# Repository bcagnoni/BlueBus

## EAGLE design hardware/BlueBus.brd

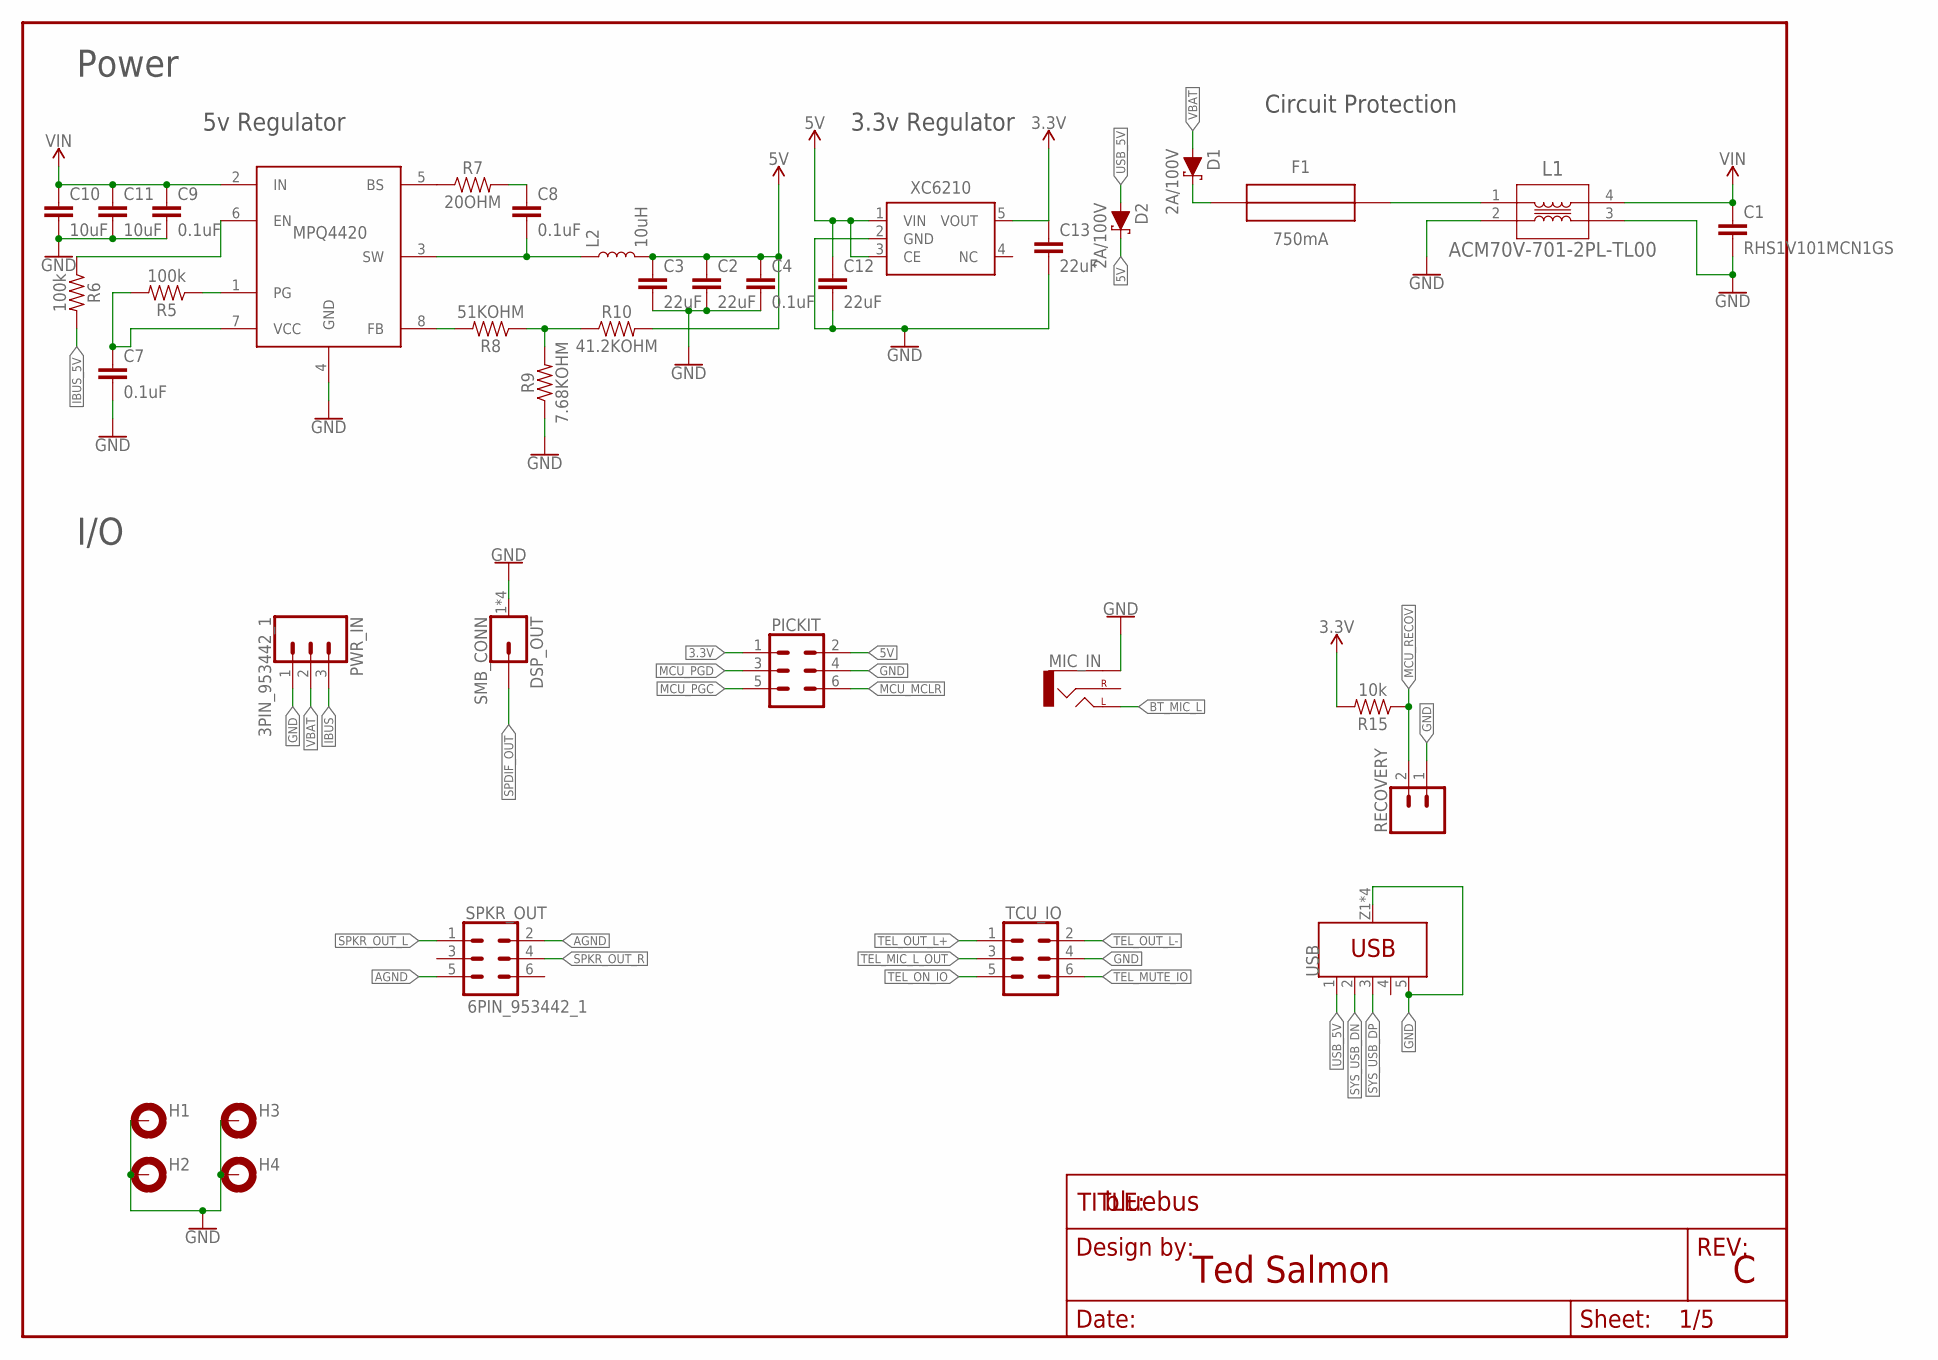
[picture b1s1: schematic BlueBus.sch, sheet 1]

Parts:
C1: RHS1V101MCN1GS
C2, C3, C12, C13: 22uF; 0805
C4, C7, C8, C9: 0.1uF; 0805
C10, C11: 10uF; 1206
D1, D2: 2A/100V; SOD123
DSP_OUT: SMB_CONN; MOLEX_SMB
F1: 750mA; LITTLEFUSE
FRAME1: FRAME-LETTER; DUMMY
H1, H2, H3, H4: 2,0-PAD; 2.0-PAD
L1: ACM70V-701-2PL-TL00
L2: 10uH; MPL-SE5040
MIC_IN: AUDIO-CUI-SJ-3523-SMT; AUDIO-CUI-SJ-352X-SMT
MPQ4420: MPQ4420; TSOT23-8
PICKIT: 6PIN_JUMPER; 2X3
PWR_IN: 3PIN_953442_1; TE_MQS_3PIN
R5, R6: 100k; 0805
R7: 20OHM; 0805
R8: 51KOHM; 0805
R9: 7.68KOHM; 0805
R10: 41.2KOHM; 0805
R15: 10k; 0805
RECOVERY: 2PIN_JUMPER; 1X02
SPKR_OUT: 6PIN_953442_1; TE_MQS_6PIN
TCU_IO: 6PIN_5_103166_1; TE_AMPMODU_6_PIN
USB: USB_WURTH_629105150521; 629105150521
XC6210: XC6210SOT25; SOT23-5

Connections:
3.3V: C13.1, PICKIT.1, R15.2, XC6210.5 (VOUT); also elsewhere on the board
5V: C2.1, C3.1, C4.1, C12.1, D2.C, L2.2, PICKIT.2, R10.2, XC6210.1 (VIN), XC6210.3 (CE); also elsewhere on the board
5VREG_BS: MPQ4420.5 (BS), R7.1
5VREG_BS_CAP: C8.1, R7.2
5VREG_EN: MPQ4420.6 (EN), R6.1
5VREG_FB: MPQ4420.8 (FB), R8.2
5VREG_FB_T: R8.1, R9.2, R10.1
5VREG_PG: MPQ4420.1 (PG), R5.1
5VREG_SW: C8.2, L2.1, MPQ4420.3 (SW)
5VREG_VCC: C7.1, MPQ4420.7 (VCC), R5.2
AGND: SPKR_OUT.2, SPKR_OUT.5; also elsewhere on the board
BT_MIC_L: MIC_IN.TIP (LEFT); also elsewhere on the board
GND: C1.2, C2.2, C3.2, C4.2, C7.2, C9.2, C10.2, C11.2, C12.2, C13.2, DSP_OUT.1 (GND), DSP_OUT.2 (GND), DSP_OUT.3 (GND), DSP_OUT.4 (GND), H1.B2,0, H2.B2,0, H3.B2,0, H4.B2,0, L1.2, L1.3, MIC_IN.SLEEVE, MPQ4420.4 (GND), PICKIT.4, PWR_IN.1, R9.1, RECOVERY.1, TCU_IO.4, USB.5 (GND), USB.Z1 (SHIELD), USB.Z2 (SHIELD), USB.Z3 (SHIELD), USB.Z4 (SHIELD), XC6210.2 (GND); also elsewhere on the board
IBUS: PWR_IN.3; also elsewhere on the board
IBUS_5V: R6.2; also elsewhere on the board
MCU_MCLR: PICKIT.6; also elsewhere on the board
MCU_PGC: PICKIT.5; also elsewhere on the board
MCU_PGD: PICKIT.3; also elsewhere on the board
MCU_RECOV: R15.1, RECOVERY.2; also elsewhere on the board
SPDIF_OUT: DSP_OUT.P$1 (1); also elsewhere on the board
SPKR_OUT_L: SPKR_OUT.1; also elsewhere on the board
SPKR_OUT_R: SPKR_OUT.4; also elsewhere on the board
SYS_USB_DN: USB.2 (D-); also elsewhere on the board
SYS_USB_DP: USB.3 (D+); also elsewhere on the board
TEL_MIC_L_OUT: TCU_IO.3; also elsewhere on the board
TEL_MUTE_IO: TCU_IO.6; also elsewhere on the board
TEL_ON_IO: TCU_IO.5; also elsewhere on the board
TEL_OUT_L+: TCU_IO.1; also elsewhere on the board
TEL_OUT_L-: TCU_IO.2; also elsewhere on the board
USB_5V: D2.A, USB.1 (VBUS)
VBAT: D1.A, PWR_IN.2
VBAT_DIODE: D1.C, F1.IN (OUT)
VBAT_FUSE: F1.OUT (IN), L1.1
VIN: C1.1, C9.1, C10.1, C11.1, L1.4, MPQ4420.2 (IN); also elsewhere on the board

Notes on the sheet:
Ted Salmon
Power
I/O
3.3v Regulator
5v Regulator
Circuit Protection

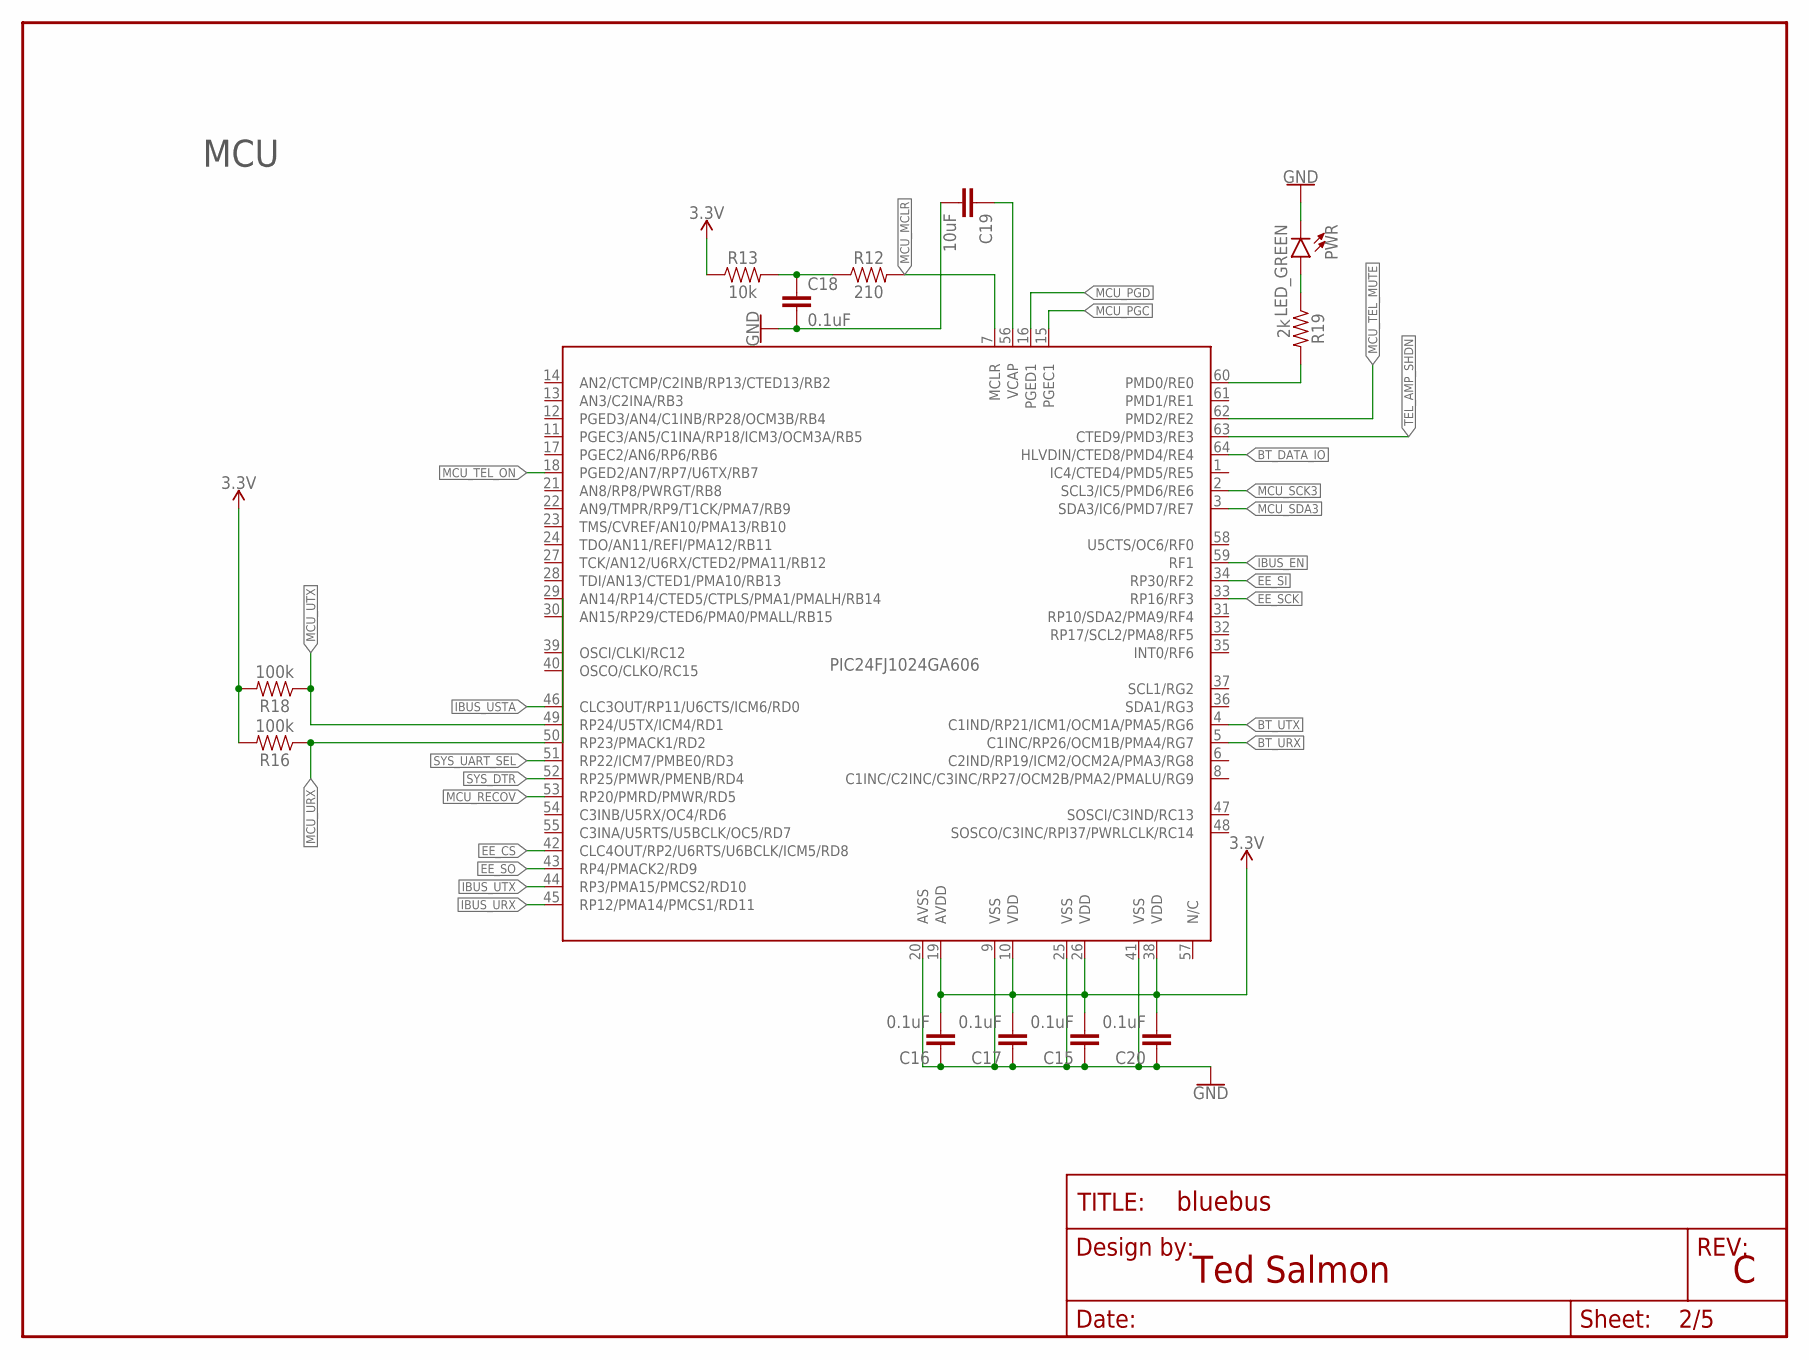
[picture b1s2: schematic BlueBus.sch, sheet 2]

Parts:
C15, C16, C17, C18, C20: 0.1uF; 0805
C19: 10uF; 0805
FRAME2: FRAME-LETTER; DUMMY
PIC24FJ1024GA606: PIC24FJ1024GA606; TQFP64
PWR: LED_GREEN; LED-0805
R12: 210; 0805
R13: 10k; 0805
R16, R18: 100k; 0805
R19: 2k; 0805

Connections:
3.3V: C15.2, C16.2, C17.2, C20.2, PIC24FJ1024GA606.10 (VDD), PIC24FJ1024GA606.19 (AVDD), PIC24FJ1024GA606.26 (VDD), PIC24FJ1024GA606.38 (VDD), R13.1, R16.2, R18.2; also elsewhere on the board
BT_DATA_IO: PIC24FJ1024GA606.64 (HLVDIN/CTED8/PMD4/RE4); also elsewhere on the board
BT_URX: PIC24FJ1024GA606.5 (C1INC/RP26/OCM1B/PMA4/RG7); also elsewhere on the board
BT_UTX: PIC24FJ1024GA606.4 (C1IND/RP21/ICM1/OCM1A/PMA5/RG6); also elsewhere on the board
EE_CS: PIC24FJ1024GA606.42 (CLC4OUT/RP2/U6RTS/U6BCLK/ICM5/RD8); also elsewhere on the board
EE_SCK: PIC24FJ1024GA606.33 (RP16/RF3); also elsewhere on the board
EE_SI: PIC24FJ1024GA606.34 (RP30/RF2); also elsewhere on the board
EE_SO: PIC24FJ1024GA606.43 (RP4/PMACK2/RD9); also elsewhere on the board
GND: C15.1, C16.1, C17.1, C18.2, C19.2, C20.1, PIC24FJ1024GA606.9 (VSS), PIC24FJ1024GA606.20 (AVSS), PIC24FJ1024GA606.25 (VSS), PIC24FJ1024GA606.41 (VSS), PWR.- (C); also elsewhere on the board
IBUS_EN: PIC24FJ1024GA606.59 (RF1); also elsewhere on the board
IBUS_URX: PIC24FJ1024GA606.45 (RP12/PMA14/PMCS1/RD11); also elsewhere on the board
IBUS_USTA: PIC24FJ1024GA606.46 (CLC3OUT/RP11/U6CTS/ICM6/RD0); also elsewhere on the board
IBUS_UTX: PIC24FJ1024GA606.44 (RP3/PMA15/PMCS2/RD10); also elsewhere on the board
MCU_MCLR: PIC24FJ1024GA606.7 (MCLR), R12.2; also elsewhere on the board
MCU_MCLR_RES: C18.1, R12.1, R13.2
MCU_ON_LED: PIC24FJ1024GA606.60 (PMD0/RE0), R19.2
MCU_ON_LED_RES: PWR.+ (A), R19.1
MCU_PGC: PIC24FJ1024GA606.15 (PGEC1); also elsewhere on the board
MCU_PGD: PIC24FJ1024GA606.16 (PGED1); also elsewhere on the board
MCU_RECOV: PIC24FJ1024GA606.53 (RP20/PMRD/PMWR/RD5); also elsewhere on the board
MCU_SCK3: PIC24FJ1024GA606.2 (SCL3/IC5/PMD6/RE6); also elsewhere on the board
MCU_SDA3: PIC24FJ1024GA606.3 (SDA3/IC6/PMD7/RE7); also elsewhere on the board
MCU_TEL_MUTE: PIC24FJ1024GA606.62 (PMD2/RE2); also elsewhere on the board
MCU_TEL_ON: PIC24FJ1024GA606.18 (PGED2/AN7/RP7/U6TX/RB7); also elsewhere on the board
MCU_URX: PIC24FJ1024GA606.50 (RP23/PMACK1/RD2), R16.1; also elsewhere on the board
MCU_UTX: PIC24FJ1024GA606.49 (RP24/U5TX/ICM4/RD1), R18.1; also elsewhere on the board
MCU_VCAP: C19.1, PIC24FJ1024GA606.56 (VCAP)
SYS_DTR: PIC24FJ1024GA606.52 (RP25/PMWR/PMENB/RD4); also elsewhere on the board
SYS_UART_SEL: PIC24FJ1024GA606.51 (RP22/ICM7/PMBE0/RD3); also elsewhere on the board
TEL_AMP_SHDN: PIC24FJ1024GA606.63 (CTED9/PMD3/RE3); also elsewhere on the board

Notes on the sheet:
Ted Salmon
MCU

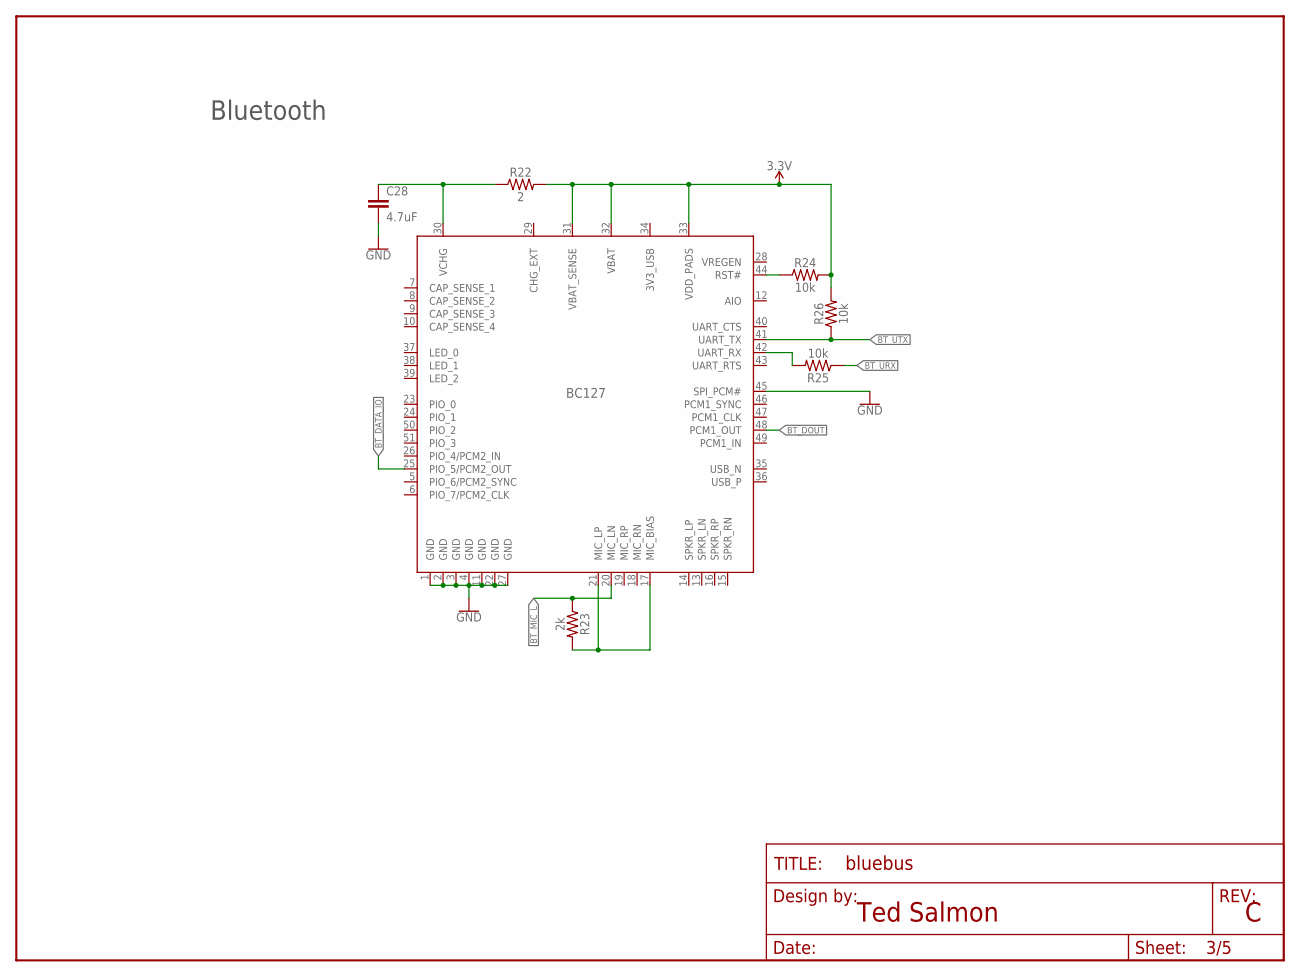
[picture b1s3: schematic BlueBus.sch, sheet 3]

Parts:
BC127: BC127
C28: 4.7uF; 0805
FRAME4: FRAME-LETTER; DUMMY
R22: 2; 0805
R23: 2k; 0805
R24, R25, R26: 10k; 0805

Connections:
3.3V: BC127.31 (VBAT_SENSE), BC127.32 (VBAT), BC127.33 (VDD_PADS), R22.2, R24.2, R26.2; also elsewhere on the board
3V3_USB: BC127.34 (3V3_USB)
BT_3V3_FILTER: BC127.30 (VCHG), C28.1, R22.1
BT_DATA_IO: BC127.25 (PIO_5/PCM2_OUT); also elsewhere on the board
BT_DOUT: BC127.48 (PCM1_OUT); also elsewhere on the board
BT_MIC_BIAS: BC127.17 (MIC_BIAS), BC127.21 (MIC_LP), R23.2
BT_MIC_L: BC127.20 (MIC_LN), R23.1; also elsewhere on the board
BT_RST: BC127.44 (RST#), R24.1
BT_URX: R25.1; also elsewhere on the board
BT_URX_RES: BC127.42 (UART_RX), R25.2
BT_UTX: BC127.41 (UART_TX), R26.1; also elsewhere on the board
CHG_EXT: BC127.29 (CHG_EXT)
GND: BC127.1 (GND), BC127.2 (GND), BC127.3 (GND), BC127.4 (GND), BC127.11 (GND), BC127.22 (GND), BC127.27 (GND), BC127.45 (SPI_PCM#), C28.2; also elsewhere on the board

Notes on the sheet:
Bluetooth
Ted Salmon

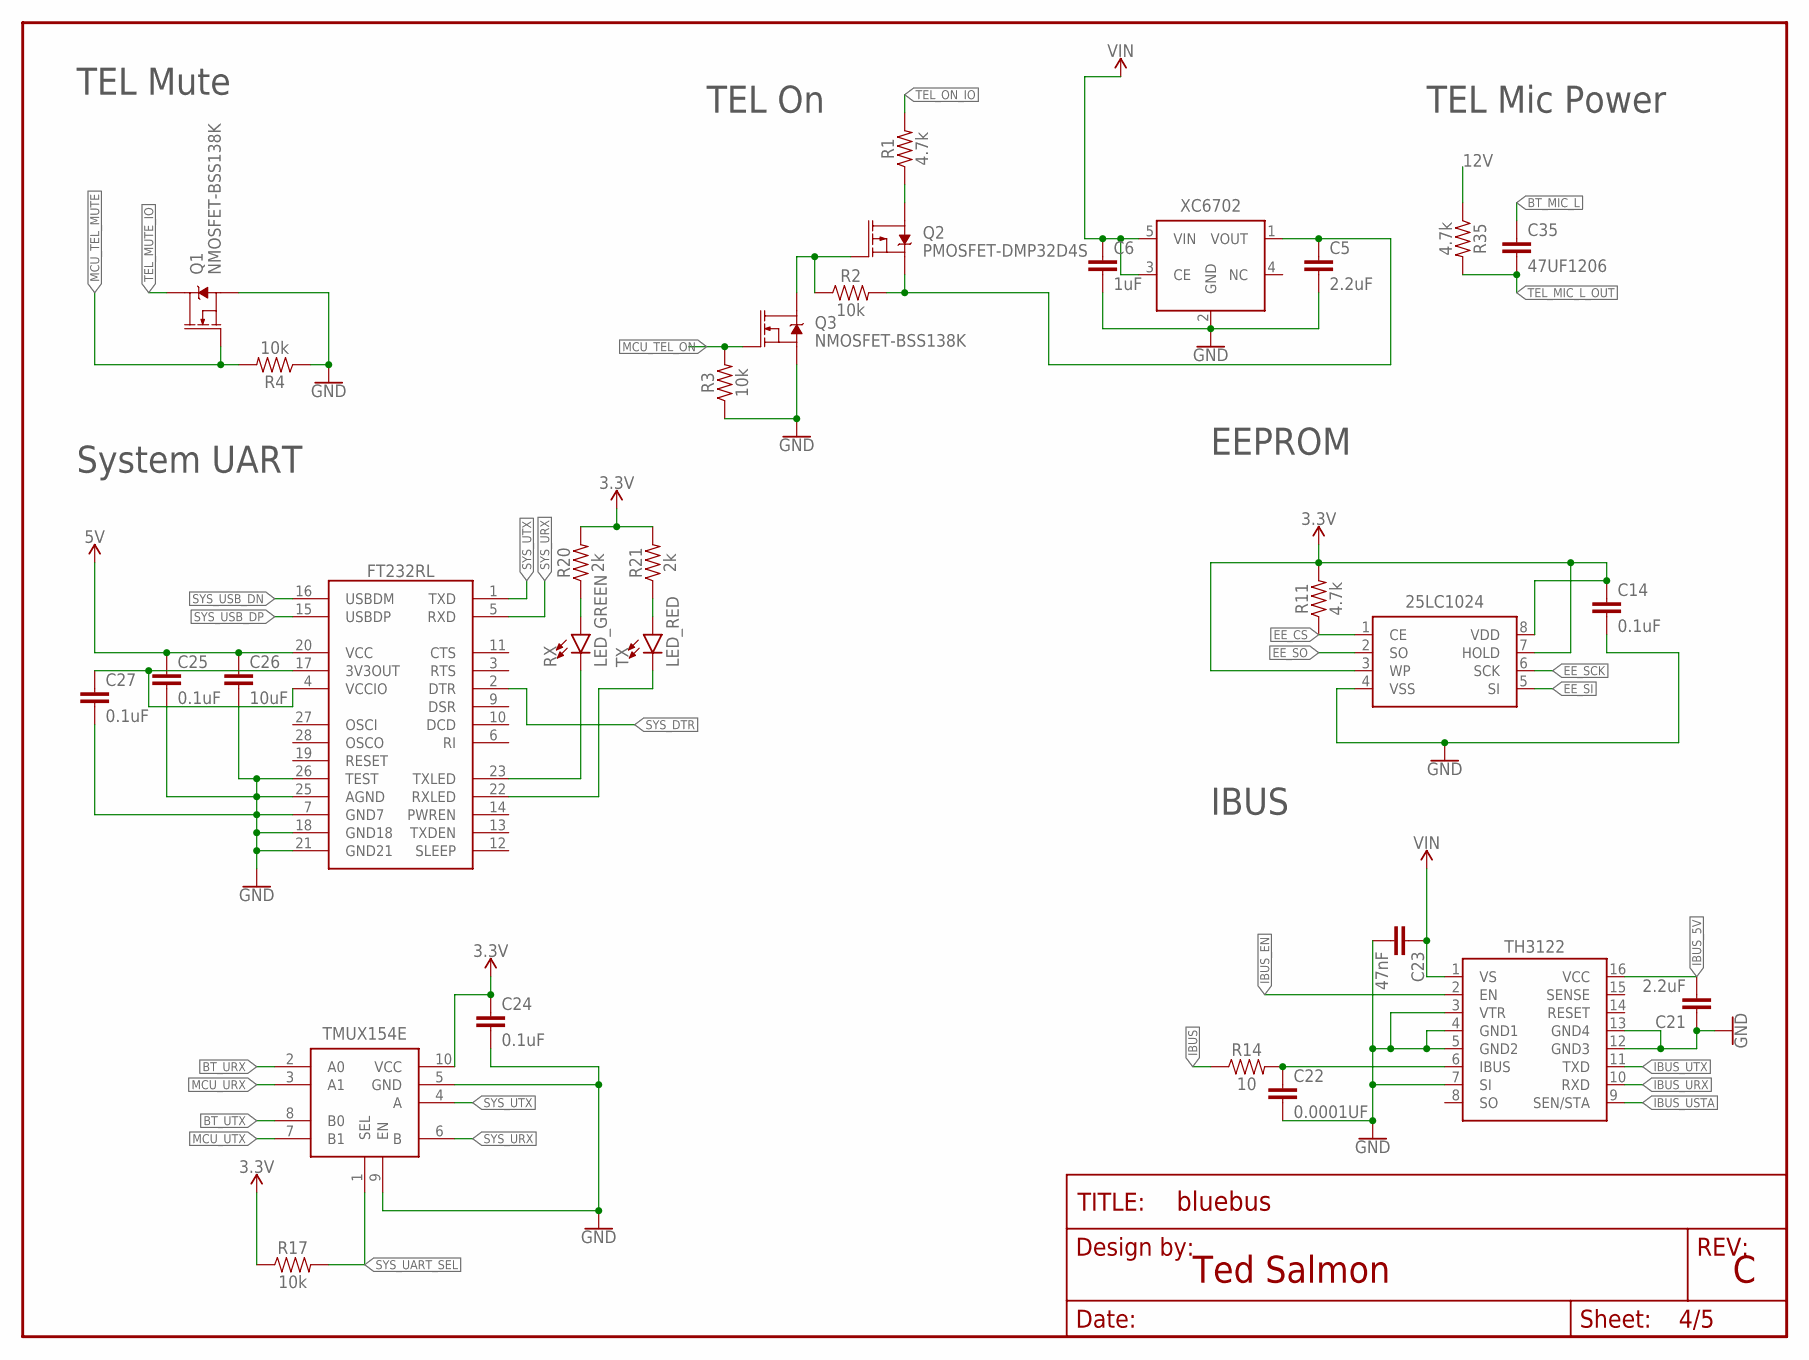
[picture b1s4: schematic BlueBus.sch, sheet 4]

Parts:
25LC1024: 25LC1024; SOIJ-8
C5, C21: 2.2uF; 0805
C6: 1uF; 0805
C14, C24, C25, C27: 0.1uF; 0805
C22: 0.0001UF; 0805
C23: 47nF; 0805
C26: 10uF; 0805
C35: 47UF1206; 1206
FRAME3: FRAME-LETTER; DUMMY
FT232RL: FT232RL; SSOP28
Q1, Q3: NMOSFET-BSS138K; SOT-23
Q2: PMOSFET-DMP32D4S; SOT-23
R1, R11, R35: 4.7k; 0805
R2, R3, R4, R17: 10k; 0805
R14: 10; 0805
R20, R21: 2k; 0805
RX: LED_GREEN; LED-0805
TH3122: TH3122.4; SOIC16DF
TMUX154E: TMUX154E; VSSOP10
TX: LED_RED; LED-0805
XC6702: XC6702DC018PR-G; SOT-89-5

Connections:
3.3V: 25LC1024.3 (WP), 25LC1024.7 (HOLD), 25LC1024.8 (VDD), C14.1, C24.1, R11.2, R17.1, R20.2, R21.2, TMUX154E.10 (VCC); also elsewhere on the board
5V: C25.1, C26.1, FT232RL.20 (VCC); also elsewhere on the board
12V: C5.1, Q2.2 (S), R2.2, R35.1, XC6702.1 (VOUT)
BT_MIC_L: C35.1; also elsewhere on the board
BT_URX: TMUX154E.2 (A0); also elsewhere on the board
BT_UTX: TMUX154E.8 (B0); also elsewhere on the board
EE_CS: 25LC1024.1 (CE), R11.1; also elsewhere on the board
EE_SCK: 25LC1024.6 (SCK); also elsewhere on the board
EE_SI: 25LC1024.5 (SI); also elsewhere on the board
EE_SO: 25LC1024.2 (SO); also elsewhere on the board
GND: 25LC1024.4 (VSS), C5.2, C6.2, C14.2, C21.1, C22.2, C23.2, C24.2, C25.2, C26.2, C27.2, FT232RL.7 (GND7), FT232RL.18 (GND18), FT232RL.21 (GND21), FT232RL.25 (AGND), FT232RL.26 (TEST), Q1.2 (S), Q3.2 (S), R3.1, R4.1, TH3122.3 (VTR), TH3122.4 (GND1), TH3122.5 (GND2), TH3122.7 (SI), TH3122.12 (GND3), TH3122.13 (GND4), TMUX154E.5 (GND), TMUX154E.9 (EN), XC6702.2 (GND); also elsewhere on the board
IBUS: R14.1; also elsewhere on the board
IBUS_5V: C21.2, TH3122.16 (VCC); also elsewhere on the board
IBUS_EN: TH3122.2 (EN); also elsewhere on the board
IBUS_FILT: C22.1, R14.2, TH3122.6 (IBUS)
IBUS_URX: TH3122.10 (RXD); also elsewhere on the board
IBUS_USTA: TH3122.9 (SEN/STA); also elsewhere on the board
IBUS_UTX: TH3122.11 (TXD); also elsewhere on the board
MCU_TEL_MUTE: Q1.1 (G), R4.2; also elsewhere on the board
MCU_TEL_ON: Q3.1 (G), R3.2; also elsewhere on the board
MCU_URX: TMUX154E.3 (A1); also elsewhere on the board
MCU_UTX: TMUX154E.7 (B1); also elsewhere on the board
RX_LED: FT232RL.23 (TXLED), RX.- (C)
RX_LED_RES: R20.1, RX.+ (A)
SYS_3V3: C27.1, FT232RL.4 (VCCIO), FT232RL.17 (3V3OUT)
SYS_DTR: FT232RL.2 (DTR); also elsewhere on the board
SYS_UART_SEL: R17.2, TMUX154E.1 (SEL); also elsewhere on the board
SYS_URX: FT232RL.5 (RXD), TMUX154E.6 (B)
SYS_USB_DN: FT232RL.16 (USBDM); also elsewhere on the board
SYS_USB_DP: FT232RL.15 (USBDP); also elsewhere on the board
SYS_UTX: FT232RL.1 (TXD), TMUX154E.4 (A)
TEL_MIC_L_OUT: C35.2, R35.2; also elsewhere on the board
TEL_MUTE_IO: Q1.3 (D); also elsewhere on the board
TEL_ON: Q2.3 (D), R1.1
TEL_ON_EN: Q2.1 (G), Q3.3 (D), R2.1
TEL_ON_IO: R1.2; also elsewhere on the board
TX_LED: FT232RL.22 (RXLED), TX.- (C)
TX_LED_RES: R21.1, TX.+ (A)
VIN: C6.1, C23.1, TH3122.1 (VS), XC6702.3 (CE), XC6702.5 (VIN); also elsewhere on the board

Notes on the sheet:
Ted Salmon
IBUS
EEPROM
TEL On
TEL Mute
TEL Mic Power
System UART

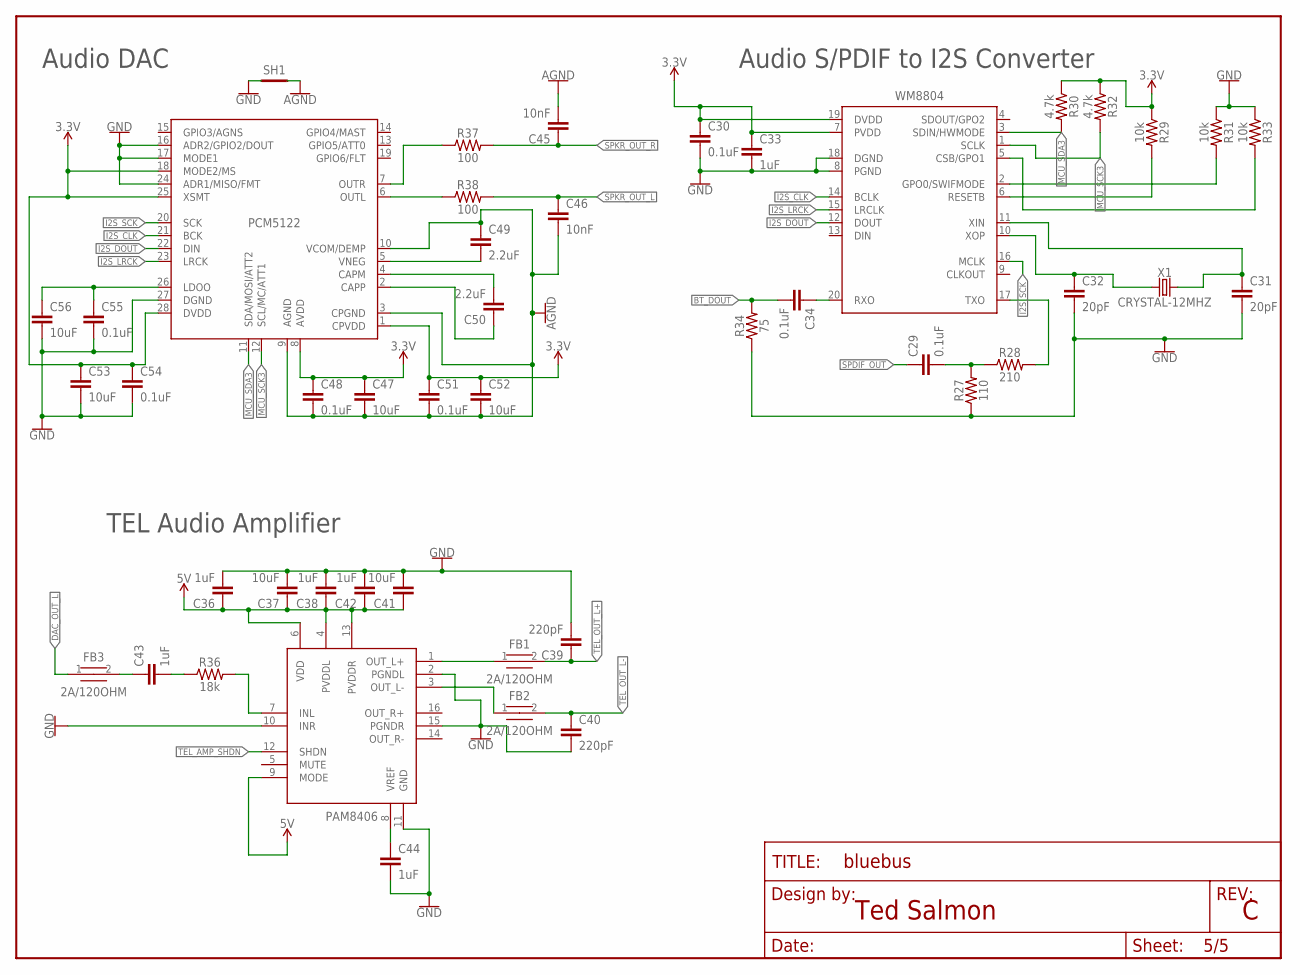
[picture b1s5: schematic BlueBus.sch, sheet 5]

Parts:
C29, C30, C34, C48, C51, C54, C55: 0.1uF; 0805
C31, C32: 20pF; 0805
C33, C36, C38, C42, C43, C44: 1uF; 0805
C37, C41, C47, C52, C53, C56: 10uF; 0805
C39, C40: 220pF; 0805
C45, C46: 10nF; 0805
C49, C50: 2.2uF; 0805
FB1, FB2, FB3: 2A/120OHM; 0805
FRAME5: FRAME-LETTER; DUMMY
PAM8406: PAM8406; SOP-16
PCM5122: PCM5122; TSSOP28
R27: 110; 0805
R28: 210; 0805
R29, R31, R33: 10k; 0805
R30, R32: 4.7k; 0805
R34: 75; 0805
R36: 18k; 0805
R37, R38: 100; 0805
SH1: SHORTT5; SHORT_TOP-50
WM8804: WM8804; SSOP20
X1: CRYSTAL-12MHZ; HC49

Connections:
3.3V: C30.1, C33.1, C47.1, C48.1, C51.1, C52.1, C53.1, C54.1, PCM5122.1 (CPVDD), PCM5122.8 (AVDD), PCM5122.18 (MODE2/MS), PCM5122.25 (XSMT), PCM5122.28 (DVDD), R29.1, R30.1, R32.1, WM8804.7 (PVDD), WM8804.19 (DVDD); also elsewhere on the board
5V: C36.1, C37.1, C38.1, C41.1, C42.1, PAM8406.4 (PVDDL), PAM8406.6 (VDD), PAM8406.9 (MODE), PAM8406.13 (PVDDR); also elsewhere on the board
AGND: C45.2, C46.2, C47.2, C48.2, C49.1, C51.2, C52.2, PCM5122.3 (CPGND), PCM5122.9 (AGND), PCM5122.10 (VCOM/DEMP), SH1.2; also elsewhere on the board
BT_DOUT: C34.2, R34.2; also elsewhere on the board
DAC_CAPM: C50.2, PCM5122.4 (CAPM)
DAC_CAPP: C50.1, PCM5122.2 (CAPP)
DAC_LDOO: C55.1, C56.1, PCM5122.26 (LDOO)
DAC_OUT_L: FB3.1, PCM5122.6 (OUTL), R38.1
DAC_OUT_R: PCM5122.7 (OUTR), R37.1
DAC_VNEG: C49.2, PCM5122.5 (VNEG)
GND: C30.2, C31.2, C32.2, C33.2, C36.2, C37.2, C38.2, C39.2, C40.2, C41.2, C42.2, C44.2, C53.2, C54.2, C55.2, C56.2, PAM8406.2 (PGNDL), PAM8406.10 (INR), PAM8406.11 (GND), PAM8406.15 (PGNDR), PCM5122.16 (ADR2/GPIO2/DOUT), PCM5122.17 (MODE1), PCM5122.24 (ADR1/MISO/FMT), PCM5122.27 (DGND), R27.1, R31.1, R33.1, R34.1, SH1.1, WM8804.8 (PGND), WM8804.18 (DGND); also elsewhere on the board
I2S_CLK: PCM5122.21 (BCK), WM8804.14 (BCLK)
I2S_DOUT: PCM5122.22 (DIN), WM8804.12 (DOUT)
I2S_LRCK: PCM5122.23 (LRCK), WM8804.15 (LRCLK)
I2S_SCK: PCM5122.20 (SCK), WM8804.16 (MCLK)
MCU_SCK3: PCM5122.12 (SCL/MC/ATT1), R32.2, WM8804.1 (SCLK); also elsewhere on the board
MCU_SDA3: PCM5122.11 (SDA/MOSI/ATT2), R30.2, WM8804.3 (SDIN/HWMODE); also elsewhere on the board
SPDIF_OUT: C29.1; also elsewhere on the board
SPDIF_RX: C34.1, WM8804.20 (RXO)
SPKR_OUT_L: C46.1, R38.2; also elsewhere on the board
SPKR_OUT_R: C45.1, R37.2; also elsewhere on the board
TEL_AMP_IN: C43.1, FB3.2
TEL_AMP_INL: PAM8406.7 (INL), R36.2
TEL_AMP_INL_CAP_RES: C43.2, R36.1
TEL_AMP_OUT_L+: FB1.1, PAM8406.1 (OUT_L+)
TEL_AMP_OUT_L-: FB2.1, PAM8406.3 (OUT_L-)
TEL_AMP_SHDN: PAM8406.12 (SHDN); also elsewhere on the board
TEL_AMP_VREF: C44.1, PAM8406.8 (VREF)
TEL_OUT_L+: C39.1, FB1.2; also elsewhere on the board
TEL_OUT_L-: C40.1, FB2.2; also elsewhere on the board
WM_CSB: R33.2, WM8804.5 (CSB/GPO1)
WM_GPO0: R31.2, WM8804.2 (GPO0/SWIFMODE)
WM_RESETB: R29.2, WM8804.6 (RESETB)
WM_SPDIF_TX_RES: R28.2, WM8804.17 (TXO)
WM_SPDIF_TX_RES2: C29.2, R27.2, R28.1
WM_XIN: C31.1, WM8804.11 (XIN), X1.2
WM_XOP: C32.1, WM8804.10 (XOP), X1.1

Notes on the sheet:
Audio DAC
Audio S/PDIF to I2S Converter
TEL Audio Amplifier
Ted Salmon

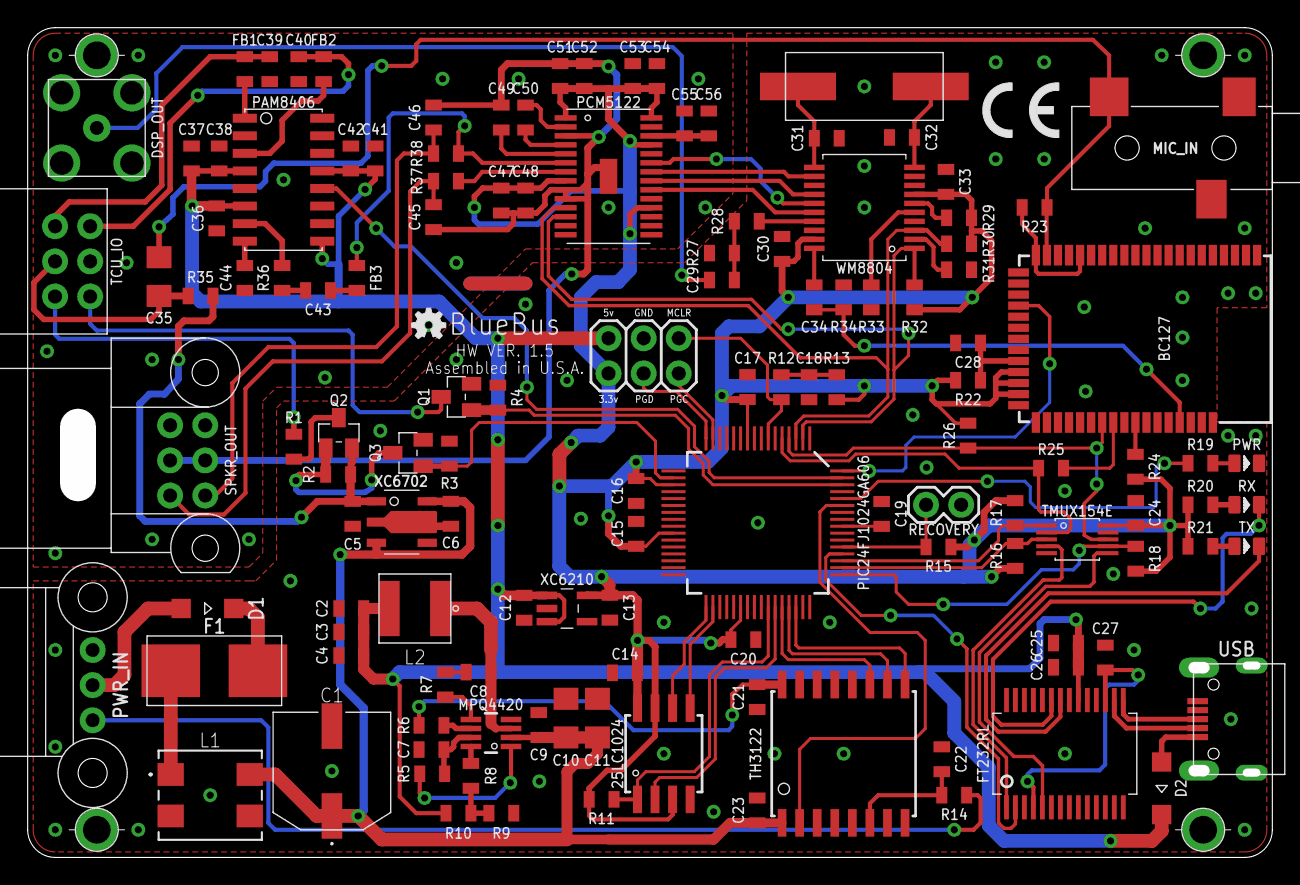
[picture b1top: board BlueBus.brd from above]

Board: 2 copper layers, 90.0 x 60.0 mm, 141 parts (0 on the bottom side), 98 nets.

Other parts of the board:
CE: CE-4MM
OSHW: OSHW-LOGO-MINI

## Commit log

2020-11-24 [IMP] hardware: v1.1.6 * Re-wire BC127 power input for use with fixed regulated voltage, rather than battery power
2020-12-05 [IMP] firmware: Application 1.1.17 * I18n improvements * Catch for BC127 boot failure. Red TEL LED is now blinked to signify a fault * Added Config "Values" rather than "Settings" * Fix "Main Menu" S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
2020-12-05 [IMP] firmware: application * Condense `Lang` selection code and fix issues with language display * Remove `Apply` from Russian language array
2020-12-05 [IMP] firmware: Application 1.1.17-beta * Allow arbitrary blinker selection for CD53/MID UI (1-8 blinks) * Add Dutch language * Update Spanish Language * Change code length to 0xA8E00 as bootloaders 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
2020-12-05 [IMP] firmware: Application Updates * Drop in German i18n * Begin support for Español * Fix Caller ID issues for multi-word callers * Improve i18n code
2020-12-05 [IMP] firmware: Application Localization Support
    * Extended ASCII symbols support fix.
    * Device name normalization fixed.
    * UtilsNormalizeText method refactoring.
    * Friendly device name size increased.
    * Defines wording update.
    * Utils char maping table updated according russified BMW Navigation firmware.
2020-12-05 [IMP] firmware: Application Localization Improvements * Rename `local` to `locale` * Alphabetize `locale` in build scripts * Remove Apply option for Language in favor of keeping all languages in the 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
2020-12-05 [IMP] utility: Mode Change and Python Env * Set Env to py3 * Add x bit to console_firmware_tool.py
2020-12-05 [IMP] firmware: Application pre-1.1.17 improvements * Support Digital audio for calls when coax cable is used * Clean up telephony volume handling code * Set max volume offset to 12 steps * Add BLE/M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
2020-12-05 [IMP] utility: Improvements * Read hex file all the way to the end of the PICs memory range (0xAA800) * Only write the blocks with opcodes present (Ignore 0xFF)
2020-12-05 [IMP] firmware: Bootloader v1.5 * Alter code so flash space up to 0xABEFF is erased when we query the device to erase flash
2020-12-05 [IMP] firmware: Application 1.1.17 beta 7 * Add Self Play ability for cars without an I-Bus Changer * Shuffle configuration parameters around
2020-12-09 [IMP] hardware: v1.6: Minor updates * Re-add 10k resistors to BC127 UART lines * Minor rewiring work around the TMUX154
2020-12-11 [IMP] harware: v1.5 updates * Replace L2 with MPL-SE5040-100 as other part is OOS * Replace C12 and C13 with 22uF capacitors * Replace 22uF capacitor part with one rated for 16v

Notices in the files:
parts and their libraries:
SparkFun-Aesthetics: Licensing: Creative Commons ShareAlike 4.0 International - https://creativecommons.org/licenses/by-sa/4.0
